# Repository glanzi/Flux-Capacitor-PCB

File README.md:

# Mini flux capacitor prop PCB

Flux capacitor from Back to the Future with 0805 LEDs, a resistor for each LED and the switch and battery holder.

This board is a clone of [Bastiaan](https://hackaday.io/bastiaan) [Mini flux capacitor prop PCB](https://hackaday.io/project/25913).

I have not tested this version, so proceed on your own risk!

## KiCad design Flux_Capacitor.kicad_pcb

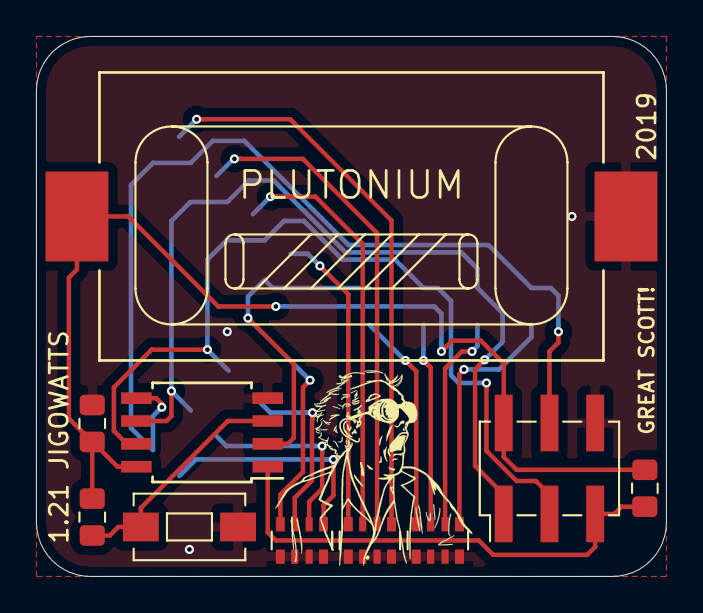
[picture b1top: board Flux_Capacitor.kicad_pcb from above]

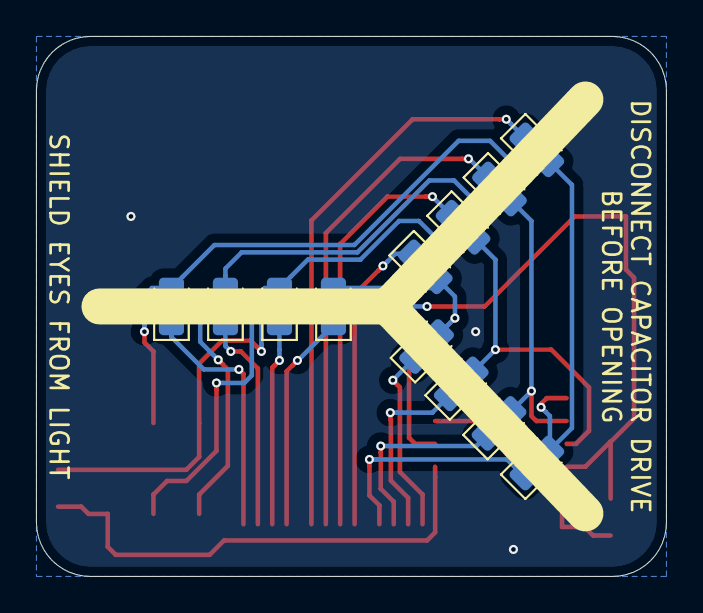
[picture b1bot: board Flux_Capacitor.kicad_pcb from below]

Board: 2 copper layers, 35.0 x 30.0 mm, 22 parts (12 on the bottom side), 20 nets.

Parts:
BT1: CR2032; BatteryHolder_MPD_BA2032SM
C1: 100nF; C_0805_2012Metric_Pad1.15x1.40mm_HandSolder
D1, D2, D3, D4, D5, D6, D7, D8, D9, D10, D11, D12: LED; LED_0805_2012Metric_Pad1.15x1.40mm_HandSolder
J1: ISP-6; PinHeader_2x03_P2.54mm_Vertical_SMD
R1, R2: 10k; R_0805_2012Metric_Pad1.15x1.40mm_HandSolder
RN1, RN2, RN3: 150; R_Array_Convex_4x0603
SW1: SW_Push; SW_SPST_EVQPE1
U1: ATtiny13A-SU; SOIJ-8_5.3x5.3mm_P1.27mm

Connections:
+3V0: BT1.1, C1.1, J1.2, R1.2, R2.2, U1.8
/MISO: D4.2, D5.2, D6.2, J1.1, U1.6
/MOSI: D1.2, D2.2, D3.2, J1.4, U1.5
/RST: J1.5, R1.1, U1.1
/SCK: D7.2, D8.2, D9.2, J1.3, U1.7
GND: BT1.2, C1.2, J1.6, RN1.1, RN1.2, RN1.3, RN1.4, RN2.1, RN2.2, RN2.3, RN2.4, RN3.1, RN3.2, RN3.3, RN3.4, SW1.1, U1.4
unnamed: D1.1, RN1.5
unnamed: D2.1, RN2.5
unnamed: D3.1, RN3.5
unnamed: D4.1, RN1.6
unnamed: D5.1, RN2.6
unnamed: D6.1, RN3.6
unnamed: D7.1, RN1.7
unnamed: D8.1, RN2.7
unnamed: D9.1, RN3.7
unnamed: D10.1, RN1.8
unnamed: D10.2, D11.2, D12.2, U1.2
unnamed: D11.1, RN2.8
unnamed: D12.1, RN3.8
unnamed: R2.1, SW1.2, U1.3

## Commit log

2019-04-28 Initial Flux Capacitor Schema
2019-05-03 Initial Flux Capacitor PCB Layout
2019-05-03 Set Design Rules
2019-05-04 Initial Routing
2019-05-29 Initial Flux Capacitor Code
2019-07-15 Initial Arduino Code
2019-07-15 Optimize Arduino Code
2019-07-15 Bill of materials
2019-07-16 Update BOM
2019-07-19 Minor code update
